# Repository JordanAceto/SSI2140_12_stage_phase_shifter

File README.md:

# SSI2140 Phase Shifter

---

## [SCHEMATIC](https://github.com/JordanAceto/SSI2140_12_stage_phase_shifter/blob/main/main_pcb/docs/SSI2140_phase_shifter-schematic.pdf)

---

### Features
- Eurorack 12 stage phase shifter
- Selectable number of stages (2, 4, 6, and 12)
- Positive and negative feedback
- Positive and negative wet/dry mix
- 1 attenuated CV input with approximately 1V/OCT response

---

## Status of the project:

Task | Status |
---------|--------------|
Schematic capture | &#9745;
PCB layout | &#9745;
Test build | &#9745;
Safe to order boards| &#9745;

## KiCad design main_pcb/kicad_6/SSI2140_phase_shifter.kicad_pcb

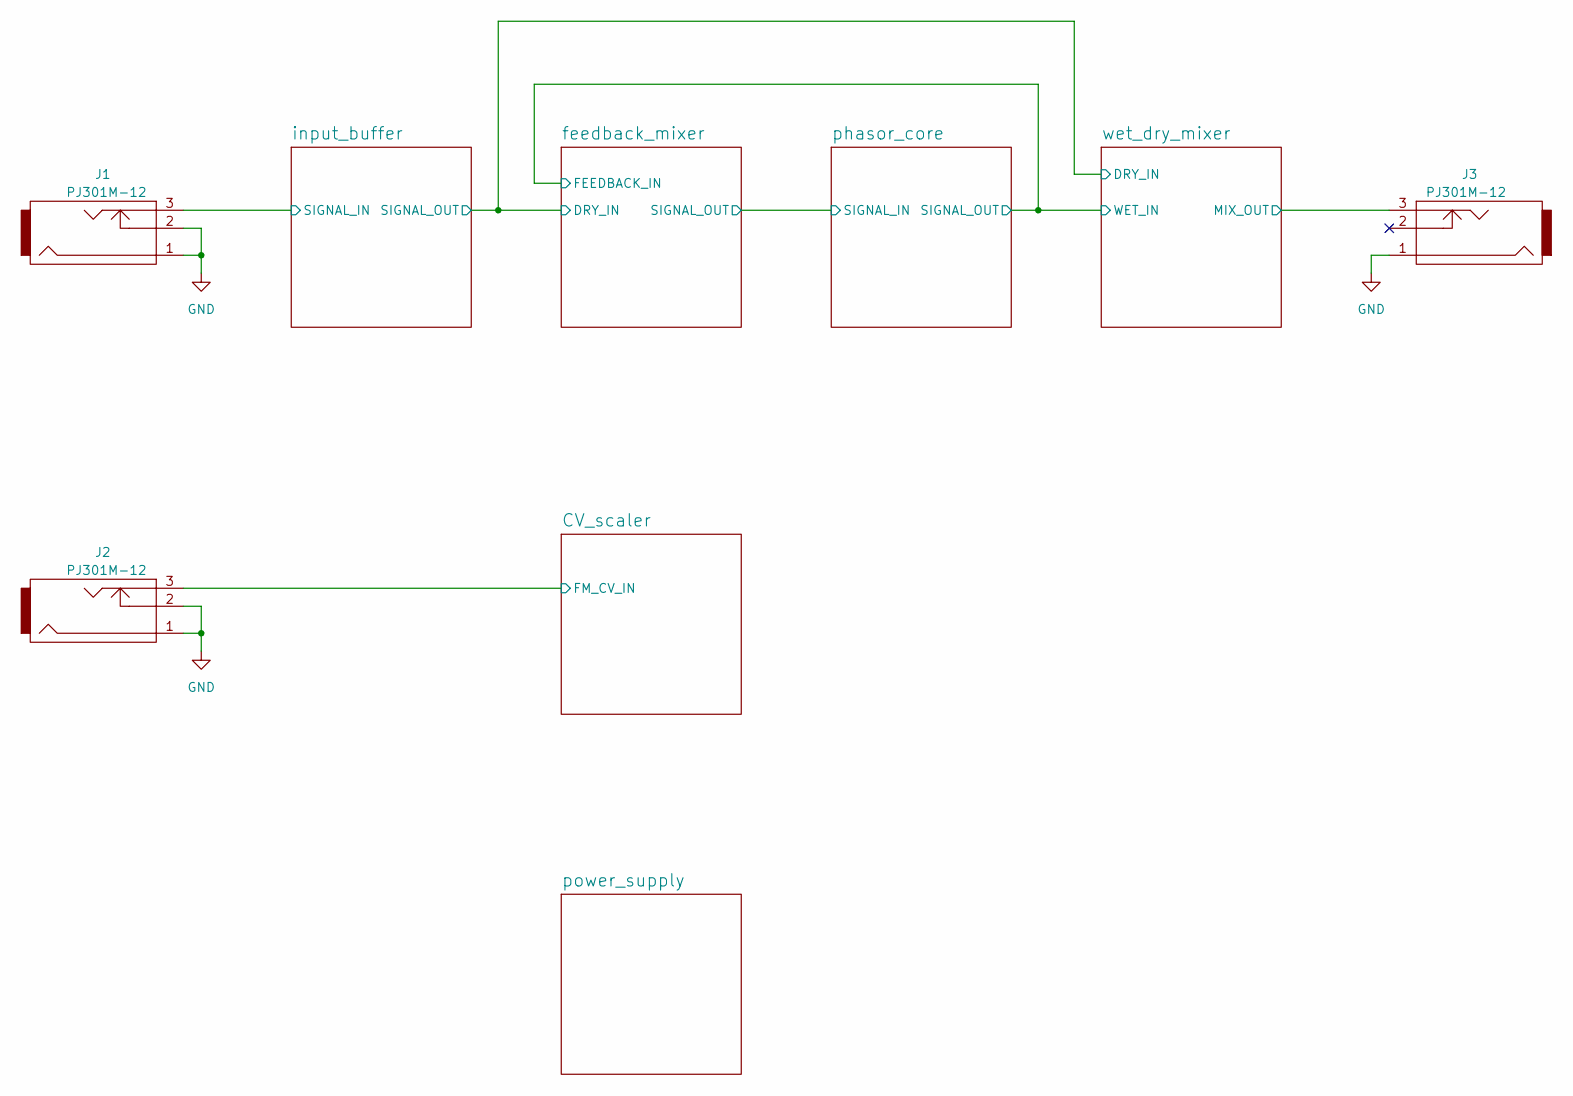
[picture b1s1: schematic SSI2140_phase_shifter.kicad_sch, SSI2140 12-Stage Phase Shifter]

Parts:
J1, J2, J3: PJ301M-12

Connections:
/CV_scaler/FM_CV_IN: J2.3; also elsewhere on the board
/input_buffer/SIGNAL_IN: J1.3; also elsewhere on the board
/wet_dry_mixer/MIX_OUT: J3.3; also elsewhere on the board
GND: J1.1, J1.2, J2.1, J2.2, J3.1; also elsewhere on the board

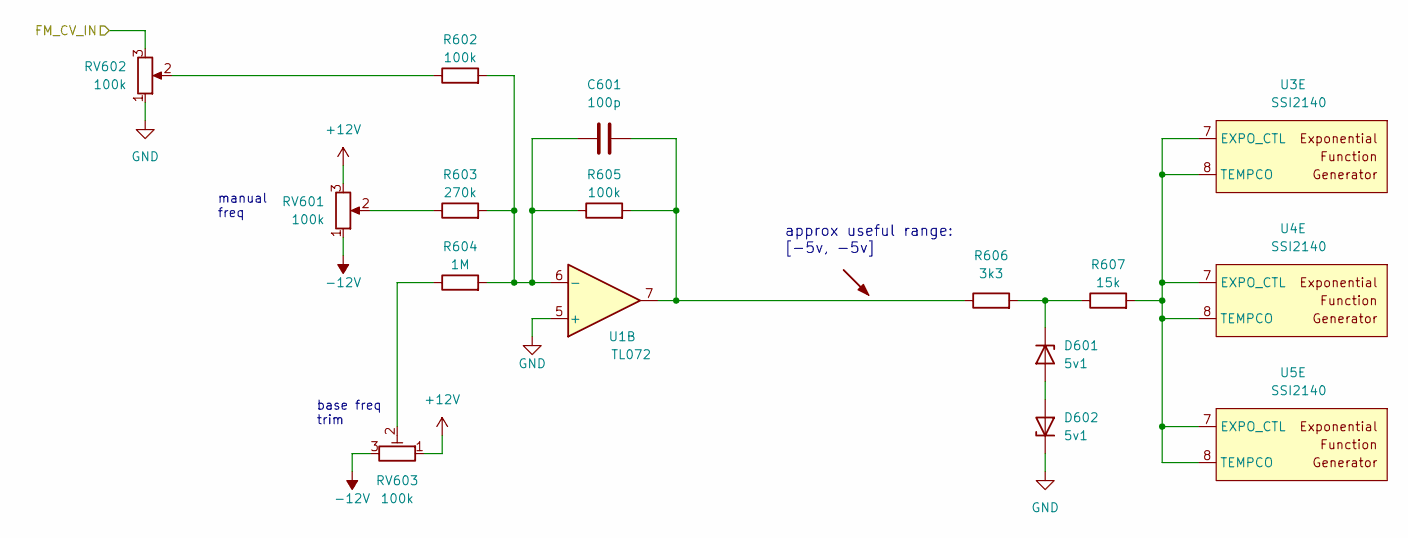
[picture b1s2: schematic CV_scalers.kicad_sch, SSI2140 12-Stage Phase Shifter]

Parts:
C601: 100p; C_0603_1608Metric
D601, D602: 5v1; D_SOD-123
R602, R605: 100k; R_0603_1608Metric
R603: 270k; R_0603_1608Metric
R604: 1M; R_0603_1608Metric
R606: 3k3; R_0603_1608Metric
R607: 15k; R_0603_1608Metric
RV601, RV602: 100k; Potentiometer_Alpha_RD901F-40-00D_Single_Vertical
RV603: 100k; Potentiometer_Bourns_3296W_Vertical
U1: TL072; SOIC-8_3.9x4.9mm_P1.27mm
U3, U4, U5: SSI2140; TSSOP-20_4.4x6.5mm_P0.65mm

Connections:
+12V: RV601.3, RV603.1; also elsewhere on the board
-12V: RV601.1, RV603.3; also elsewhere on the board
/CV_scaler/FM_CV_IN: RV602.3; also elsewhere on the board
GND: D602.1 (K), RV602.1, U1.5 (+); also elsewhere on the board
unnamed: C601.1, R602.2, R603.2, R604.2, R605.1, U1.6 (-)
unnamed: C601.2, R605.2, R606.1, U1.7
unnamed: D601.1 (K), R606.2, R607.1
unnamed: D601.2 (A), D602.2 (A)
unnamed: R602.1, RV602.2
unnamed: R603.1, RV601.2
unnamed: R604.1, RV603.2
unnamed: R607.2, U3.7 (EXPO_CTL), U3.8 (TEMPCO), U4.7 (EXPO_CTL), U4.8 (TEMPCO), U5.7 (EXPO_CTL), U5.8 (TEMPCO)

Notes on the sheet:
base freq trim
manual freq
approx useful range: [-5v, -5v]

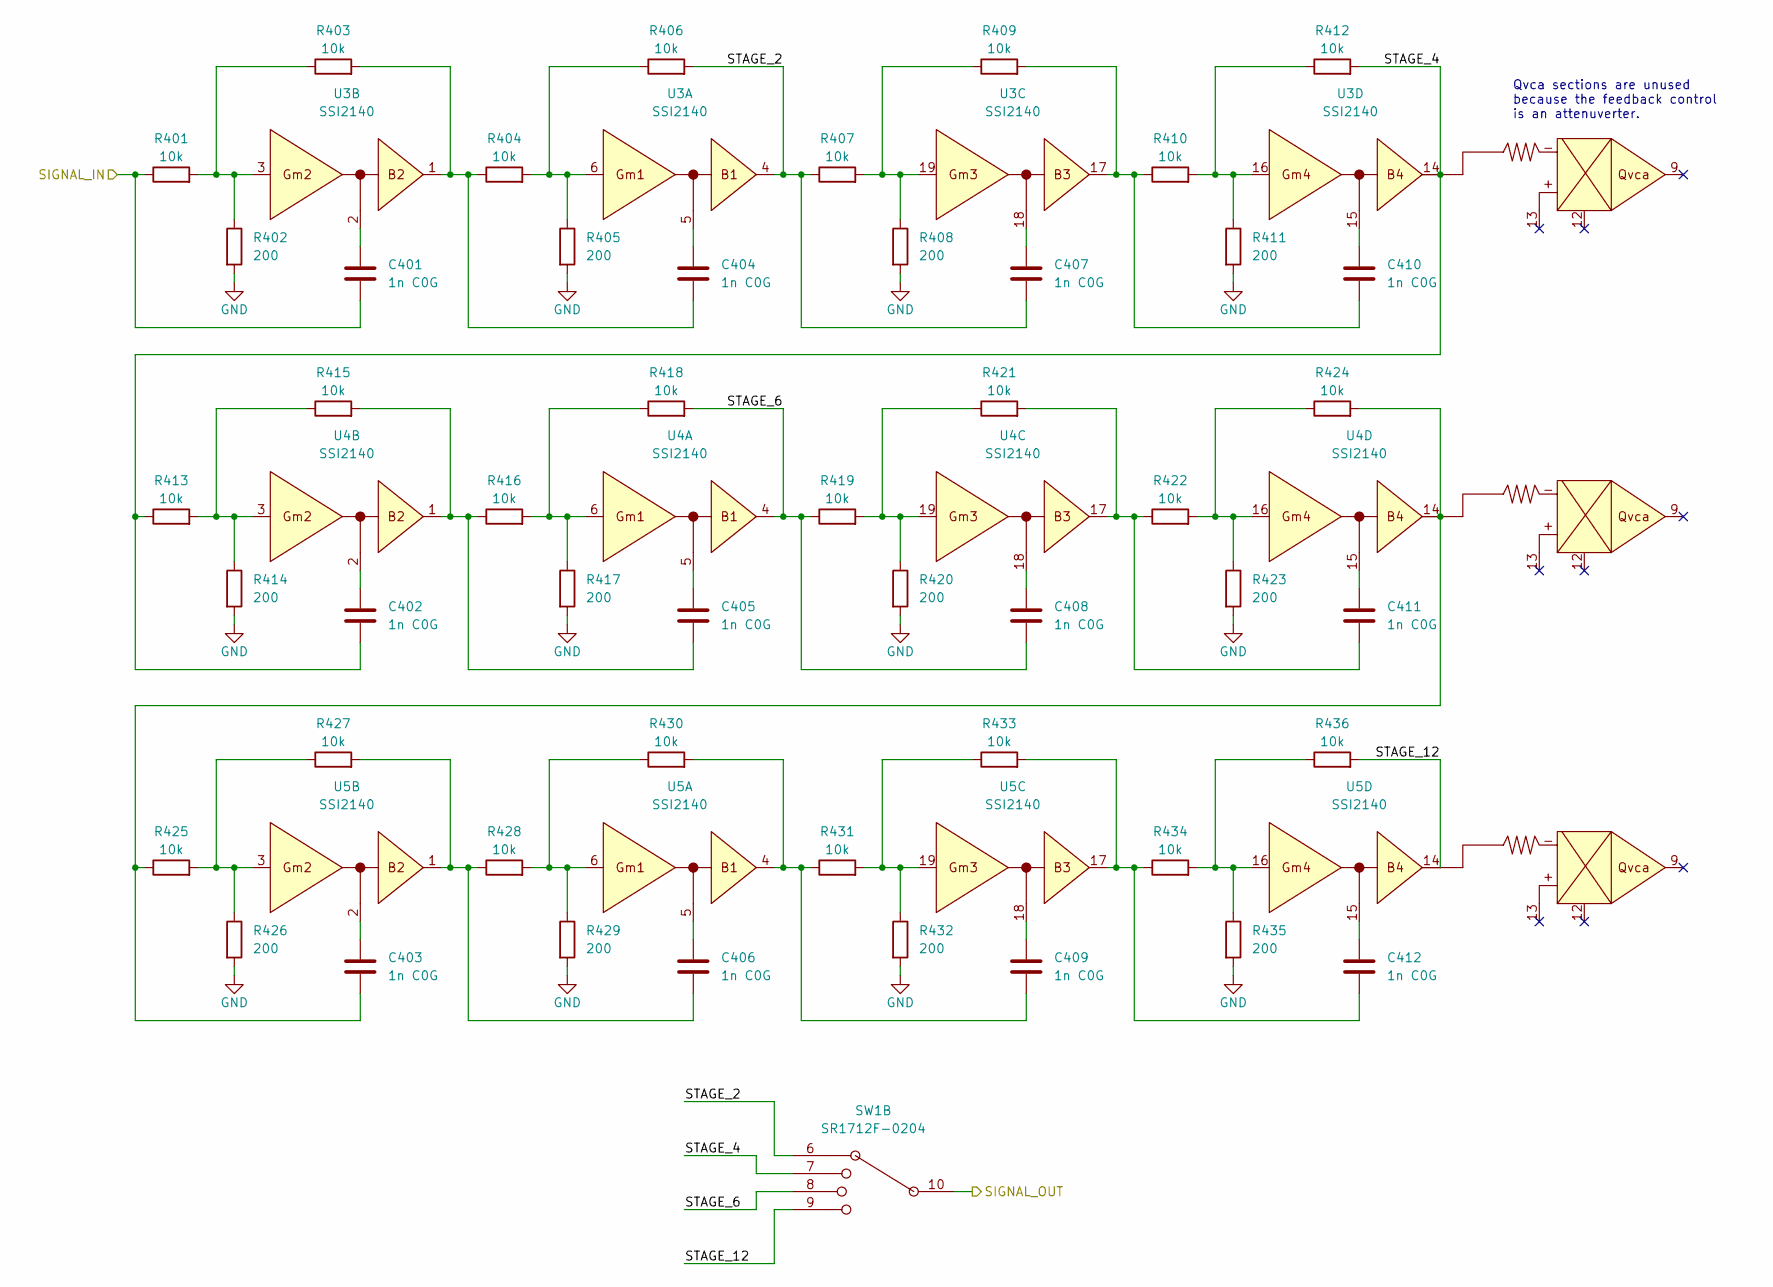
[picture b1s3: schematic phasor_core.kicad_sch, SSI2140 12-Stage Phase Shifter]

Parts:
C401, C402, C403, C404, C405, C406, C407, C408, C409, C410, C411, C412: 1n C0G; C_0805_2012Metric
R401, R403, R404, R406, R407, R409, R410, R412, R413, R415, R416, R418, R419, R421, R422, R424, R425, R427, R428, R430, R431, R433, R434, R436: 10k; R_0603_1608Metric
R402, R405, R408, R411, R414, R417, R420, R423, R426, R429, R432, R435: 200; R_0603_1608Metric
SW1: SR1712F-0204; SR1712F_rotary_switch
U3, U4, U5: SSI2140; TSSOP-20_4.4x6.5mm_P0.65mm

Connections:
/feedback_mixer/FEEDBACK_IN: SW1.10; also elsewhere on the board
/feedback_mixer/SIGNAL_OUT: C401.2, R401.1; also elsewhere on the board
/phasor_core/STAGE_2: C407.2, R406.2, R407.1, SW1.6, U3.4
/phasor_core/STAGE_4: C402.2, R412.2, R413.1, SW1.7, U3.14
/phasor_core/STAGE_6: C408.2, R418.2, R419.1, SW1.8, U4.4
/phasor_core/STAGE_12: R436.2, SW1.9, U5.14
GND: R402.2, R405.2, R408.2, R411.2, R414.2, R417.2, R420.2, R423.2, R426.2, R429.2, R432.2, R435.2; also elsewhere on the board
unnamed: C401.1, U3.2
unnamed: C402.1, U4.2
unnamed: C403.1, U5.2
unnamed: C403.2, R424.2, R425.1, U4.14
unnamed: C404.1, U3.5
unnamed: C404.2, R403.2, R404.1, U3.1
unnamed: C405.1, U4.5
unnamed: C405.2, R415.2, R416.1, U4.1
unnamed: C406.1, U5.5
unnamed: C406.2, R427.2, R428.1, U5.1
unnamed: C407.1, U3.18
unnamed: C408.1, U4.18
unnamed: C409.1, U5.18
unnamed: C409.2, R430.2, R431.1, U5.4
unnamed: C410.1, U3.15
unnamed: C410.2, R409.2, R410.1, U3.17
unnamed: C411.1, U4.15
unnamed: C411.2, R421.2, R422.1, U4.17
unnamed: C412.1, U5.15
unnamed: C412.2, R433.2, R434.1, U5.17
unnamed: R401.2, R402.1, R403.1, U3.3
unnamed: R404.2, R405.1, R406.1, U3.6
unnamed: R407.2, R408.1, R409.1, U3.19
unnamed: R410.2, R411.1, R412.1, U3.16
unnamed: R413.2, R414.1, R415.1, U4.3
unnamed: R416.2, R417.1, R418.1, U4.6
unnamed: R419.2, R420.1, R421.1, U4.19
unnamed: R422.2, R423.1, R424.1, U4.16
unnamed: R425.2, R426.1, R427.1, U5.3
unnamed: R428.2, R429.1, R430.1, U5.6
unnamed: R431.2, R432.1, R433.1, U5.19
unnamed: R434.2, R435.1, R436.1, U5.16

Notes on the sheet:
Qvca sections are unused because the feedback control is an attenuverter.

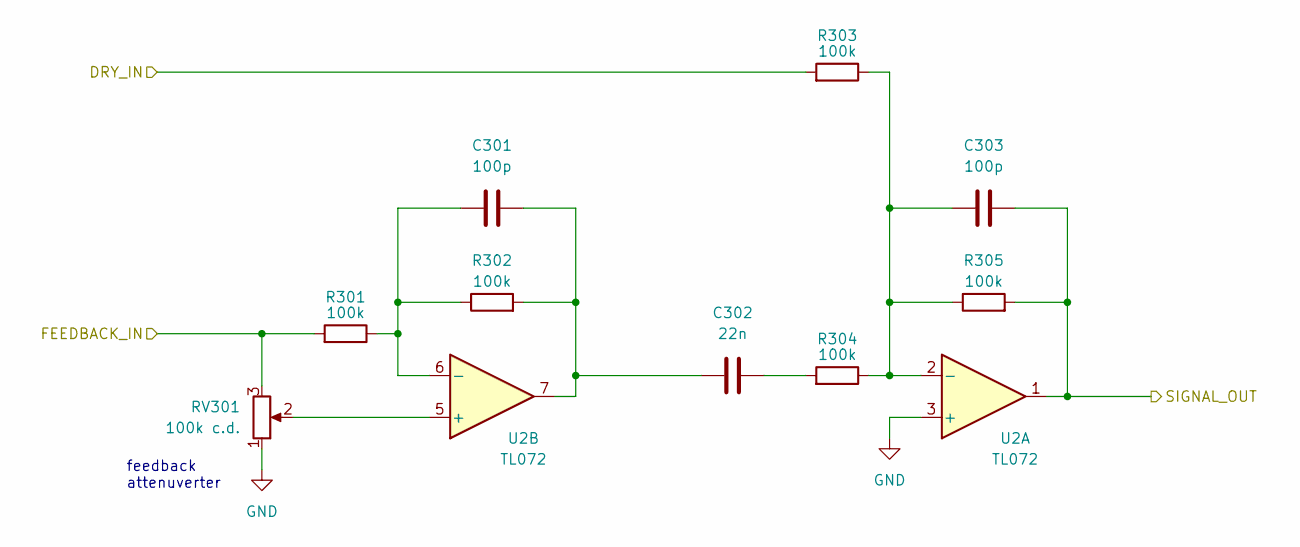
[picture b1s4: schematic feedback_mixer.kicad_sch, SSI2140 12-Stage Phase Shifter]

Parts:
C301, C303: 100p; C_0603_1608Metric
C302: 22n; C_Rect_L7.0mm_W2.5mm_P5.00mm
R301, R302, R303, R304, R305: 100k; R_0603_1608Metric
RV301: 100k c.d.; Potentiometer_Alpha_RD901F-40-00D_Single_Vertical
U2: TL072; SOIC-8_3.9x4.9mm_P1.27mm

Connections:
/feedback_mixer/DRY_IN: R303.2; also elsewhere on the board
/feedback_mixer/FEEDBACK_IN: R301.2, RV301.3; also elsewhere on the board
/feedback_mixer/SIGNAL_OUT: C303.1, R305.2, U2.1; also elsewhere on the board
GND: RV301.1, U2.3 (+); also elsewhere on the board
unnamed: C301.1, C302.1, R302.2, U2.7
unnamed: C301.2, R301.1, R302.1, U2.6 (-)
unnamed: C302.2, R304.2
unnamed: C303.2, R303.1, R304.1, R305.1, U2.2 (-)
unnamed: RV301.2, U2.5 (+)

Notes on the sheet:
feedback attenuverter

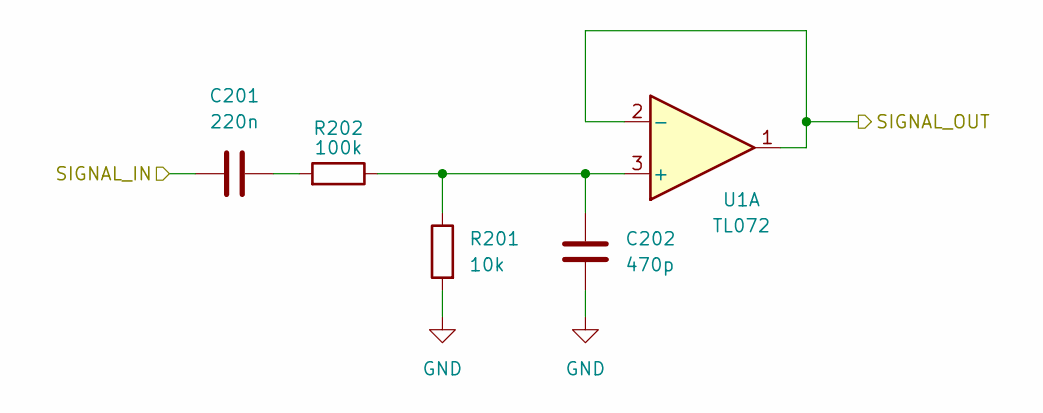
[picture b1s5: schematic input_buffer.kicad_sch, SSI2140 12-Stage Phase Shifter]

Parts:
C201: 220n; C_Rect_L7.0mm_W2.5mm_P5.00mm
C202: 470p; C_0603_1608Metric
R201: 10k; R_0603_1608Metric
R202: 100k; R_0603_1608Metric
U1: TL072; SOIC-8_3.9x4.9mm_P1.27mm

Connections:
/feedback_mixer/DRY_IN: U1.1, U1.2 (-); also elsewhere on the board
/input_buffer/SIGNAL_IN: C201.2; also elsewhere on the board
GND: C202.1, R201.2; also elsewhere on the board
unnamed: C201.1, R202.2
unnamed: C202.2, R201.1, R202.1, U1.3 (+)

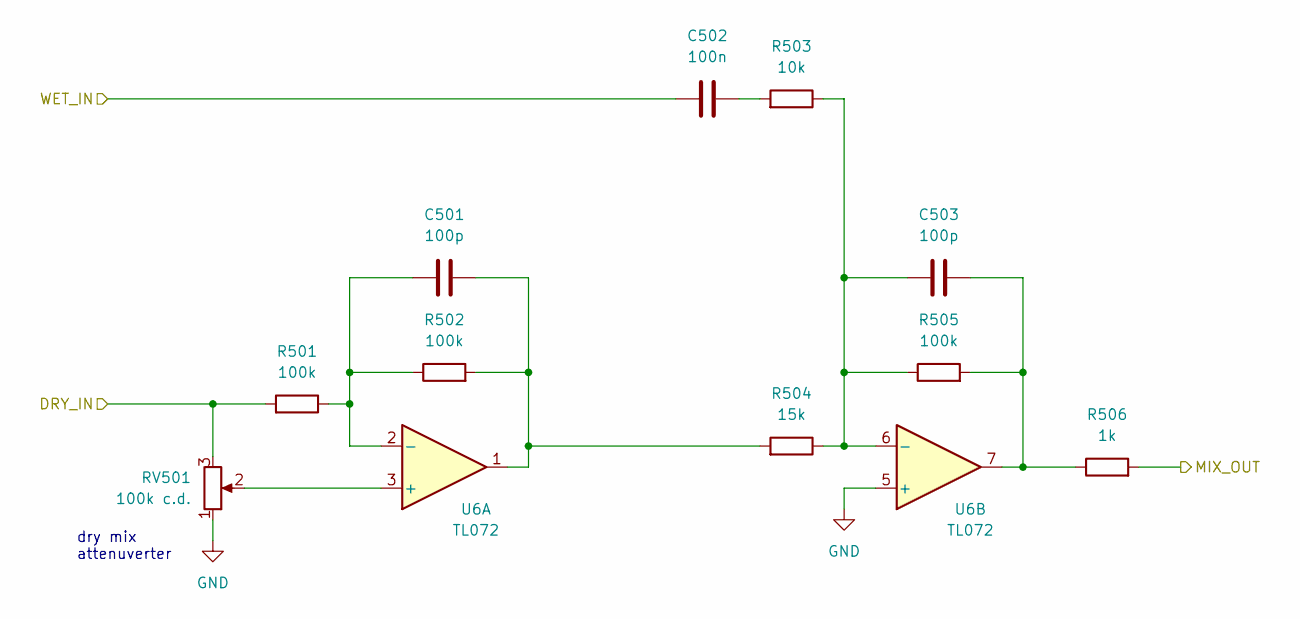
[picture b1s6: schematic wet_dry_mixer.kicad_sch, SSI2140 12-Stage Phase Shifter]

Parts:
C501, C503: 100p; C_0603_1608Metric
C502: 100n; C_Rect_L7.0mm_W2.5mm_P5.00mm
R501, R502, R505: 100k; R_0603_1608Metric
R503: 10k; R_0603_1608Metric
R504: 15k; R_0603_1608Metric
R506: 1k; R_0603_1608Metric
RV501: 100k c.d.; Potentiometer_Alpha_RD901F-40-00D_Single_Vertical
U6: TL072; SOIC-8_3.9x4.9mm_P1.27mm

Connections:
/feedback_mixer/DRY_IN: R501.2, RV501.3; also elsewhere on the board
/feedback_mixer/FEEDBACK_IN: C502.1; also elsewhere on the board
/wet_dry_mixer/MIX_OUT: R506.2; also elsewhere on the board
GND: RV501.1, U6.5 (+); also elsewhere on the board
unnamed: C501.1, R502.2, R504.2, U6.1
unnamed: C501.2, R501.1, R502.1, U6.2 (-)
unnamed: C502.2, R503.2
unnamed: C503.1, R505.2, R506.1, U6.7
unnamed: C503.2, R503.1, R504.1, R505.1, U6.6 (-)
unnamed: RV501.2, U6.3 (+)

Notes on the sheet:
dry mix attenuverter

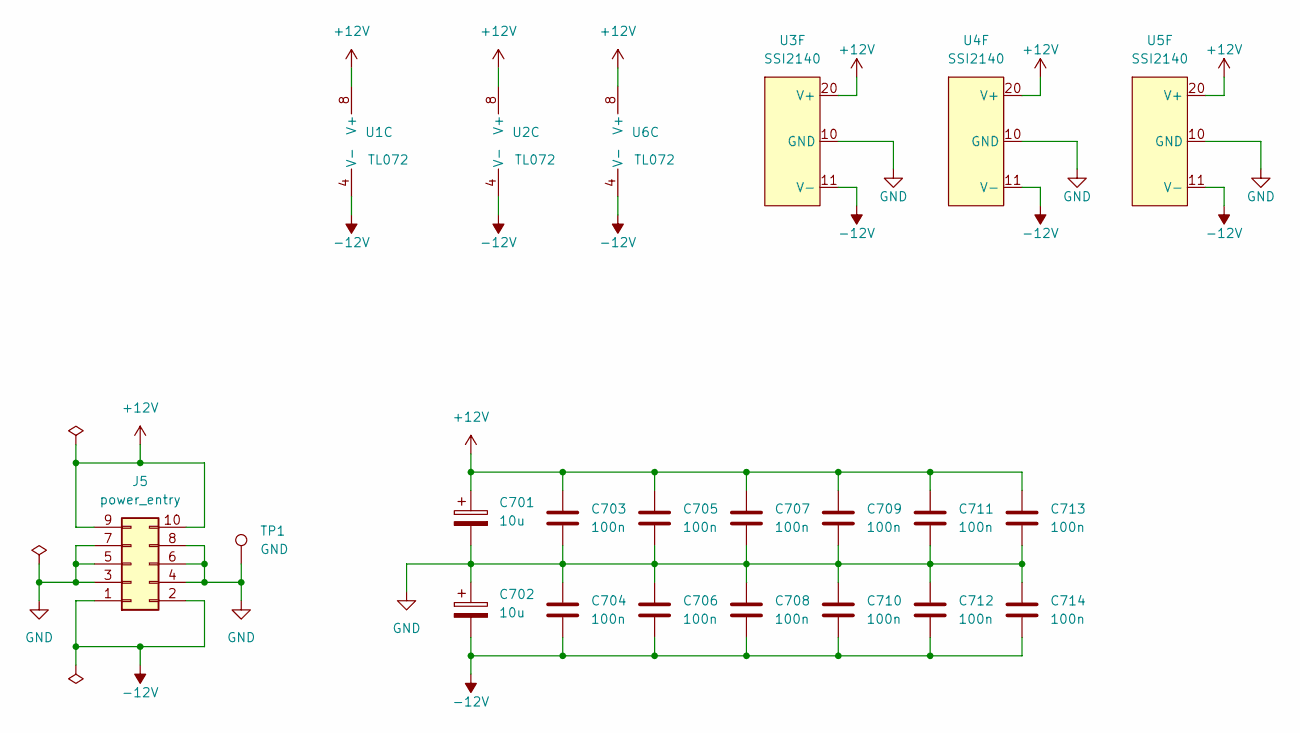
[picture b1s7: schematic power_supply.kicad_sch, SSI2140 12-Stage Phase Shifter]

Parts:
C701, C702: 10u; CP_Radial_D6.3mm_P2.50mm
C703, C704, C705, C706, C707, C708, C709, C710, C711, C712, C713, C714: 100n; C_0603_1608Metric
J5: power_entry; PinHeader_2x05_P2.54mm_Vertical
TP1: GND; TestPoint_Bridge_Pitch7.62mm_Drill1.3mm
U1, U2, U6: TL072; SOIC-8_3.9x4.9mm_P1.27mm
U3, U4, U5: SSI2140; TSSOP-20_4.4x6.5mm_P0.65mm

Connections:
+12V: C701.1, C703.1, C705.1, C707.1, C709.1, C711.1, C713.1, J5.9, J5.10, U1.8 (V+), U2.8 (V+), U3.20 (V+), U4.20 (V+), U5.20 (V+), U6.8 (V+); also elsewhere on the board
-12V: C702.2, C704.2, C706.2, C708.2, C710.2, C712.2, C714.2, J5.1, J5.2, U1.4 (V-), U2.4 (V-), U3.11 (V-), U4.11 (V-), U5.11 (V-), U6.4 (V-); also elsewhere on the board
GND: C701.2, C702.1, C703.2, C704.1, C705.2, C706.1, C707.2, C708.1, C709.2, C710.1, C711.2, C712.1, C713.2, C714.1, J5.3, J5.4, J5.5, J5.6, J5.7, J5.8, TP1.1, U3.10 (GND), U4.10 (GND), U5.10 (GND); also elsewhere on the board

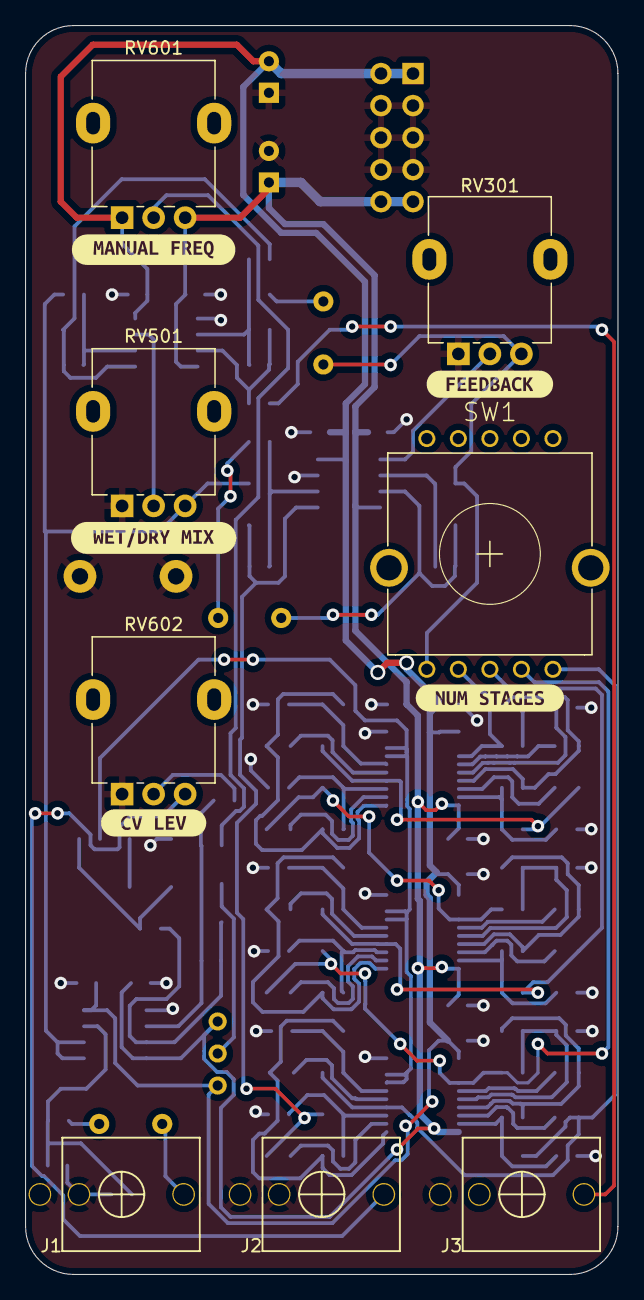
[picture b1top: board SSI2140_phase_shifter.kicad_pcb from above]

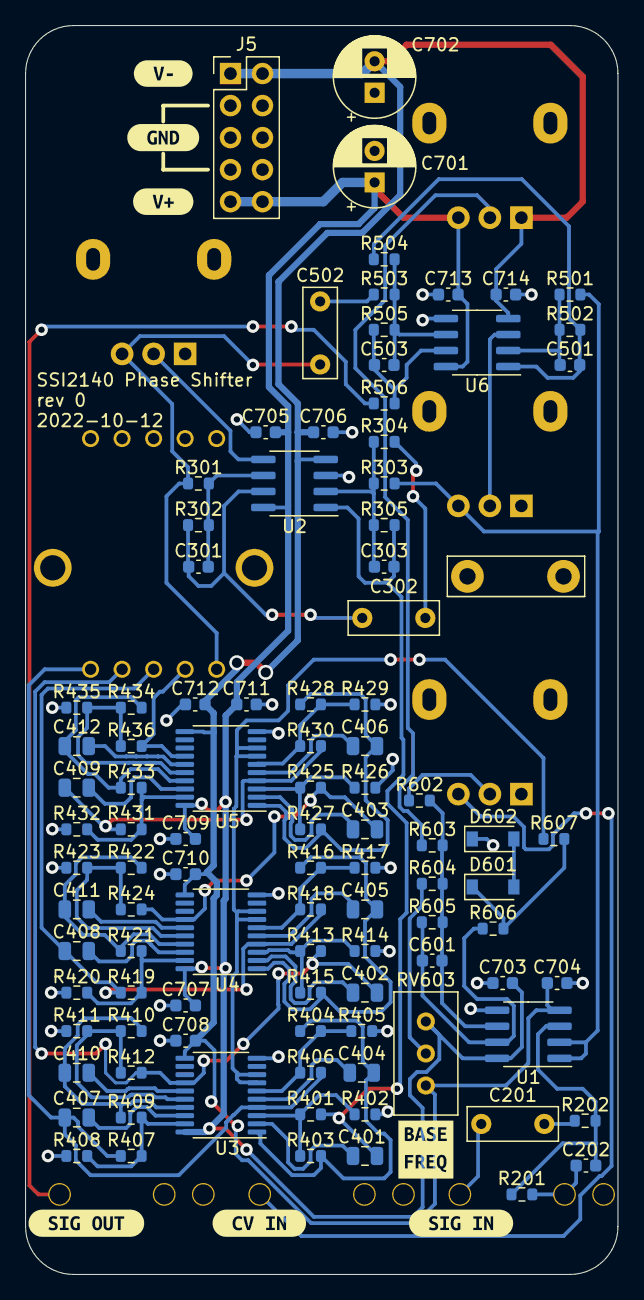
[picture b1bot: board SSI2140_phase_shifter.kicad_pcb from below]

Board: 2 copper layers, 47.0 x 99.1 mm, 121 parts (108 on the bottom side), 66 nets.

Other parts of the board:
kibuzzard-6346B9B0: G***; kibuzzard-6346B9B0
kibuzzard-6346B9BA: G***; kibuzzard-6346B9BA
kibuzzard-6346B9C8: G***; kibuzzard-6346B9C8
kibuzzard-6346BA4D: G***; kibuzzard-6346BA4D
kibuzzard-6346BA5C: G***; kibuzzard-6346BA5C
kibuzzard-6346BA18: G***; kibuzzard-6346BA18
kibuzzard-6346BA34: G***; kibuzzard-6346BA34
kibuzzard-6346BB8C: G***; kibuzzard-6346BB8C
kibuzzard-6346BB9C: G***; kibuzzard-6346BB9C
kibuzzard-6346BBAC: G***; kibuzzard-6346BBAC
kibuzzard-6346BBB6: G***; kibuzzard-6346BBB6
kibuzzard-6346BBC8: G***; kibuzzard-6346BBC8

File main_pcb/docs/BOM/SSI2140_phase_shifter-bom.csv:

Row,Description,Part,References,Value,Footprint,Quantity Per PCB,Status,Datasheet
1,Unpolarized capacitor,C,C301 C303 C501 C503 C601,100p,C_0603_1608Metric,5, ,~
2,Unpolarized capacitor,C,C202,470p,C_0603_1608Metric,1, ,~
3,Unpolarized capacitor,C,C401 C402 C403 C404 C405 C406 C407 C408 C409 C410 C411 C412,1n C0G,C_0805_2012Metric,12, ,~
4,Unpolarized capacitor,C,C302,22n,C_Rect_L7.0mm_W2.5mm_P5.00mm,1, ,~
5,Unpolarized capacitor,C,C502,100n,C_Rect_L7.0mm_W2.5mm_P5.00mm,1, ,~
6,Unpolarized capacitor,C,C703 C704 C705 C706 C707 C708 C709 C710 C711 C712 C713 C714,100n,C_0603_1608Metric,12, ,~
7,Unpolarized capacitor,C,C201,220n,C_Rect_L7.0mm_W2.5mm_P5.00mm,1, ,~
8,Polarized capacitor,C_Polarized,C701 C702,10u,CP_Radial_D6.3mm_P2.50mm,2, ,~
9,Zener diode,D_Zener,D601 D602,5v1,D_SOD-123,2, ,~
10,,PJ301M-12,J1 J2 J3,PJ301M-12,PJ301M-12,3, ,
11,"Generic connector, double row, 02x05, odd/even pin numbering scheme (row 1 odd numbers, row 2 even numbers), script generated (kicad-library-utils/schlib/autogen/connector/)",Conn_02x05_Odd_Even,J5,power_entry,PinHeader_2x05_P2.54mm_Vertical,1, ,~
12,Resistor,R,R402 R405 R408 R411 R414 R417 R420 R423 R426 R429 R432 R435,200,R_0603_1608Metric,12, ,~
13,Resistor,R,R506,1k,R_0603_1608Metric,1, ,~
14,Resistor,R,R606,3k3,R_0603_1608Metric,1, ,~
15,Resistor,R,R201 R401 R403 R404 R406 R407 R409 R410 R412 R413 R415 R416 R418 R419 R421 R422 R424 R425 R427 R428 R430 R431 R433 R434 R436 R503,10k,R_0603_1608Metric,26, ,~
16,Resistor,R,R504 R607,15k,R_0603_1608Metric,2, ,~
17,Resistor,R,R202 R301 R302 R303 R304 R305 R501 R502 R505 R602 R605,100k,R_0603_1608Metric,11, ,~
18,Resistor,R,R603,270k,R_0603_1608Metric,1, ,~
19,Resistor,R,R604,1M,R_0603_1608Metric,1, ,~
20,Potentiometer,R_Potentiometer,RV301 RV501 RV601 RV602,100k c.d.,Potentiometer_Alpha_RD901F-40-00D_Single_Vertical,4, ,~
21,Trim-potentiometer,R_Potentiometer_Trim,RV603,100k,Potentiometer_Bourns_3296W_Vertical,1, ,~
22,3 rotary switches with 4 positions,SR1712F-0204,SW1,SR1712F-0204,SR1712F_rotary_switch,1, ,
23,,SSI2140,U3 U4 U5,SSI2140,TSSOP-20_4.4x6.5mm_P0.65mm,3, ,
24,"Dual Low-Noise JFET-Input Operational Amplifiers, DIP-8/SOIC-8",TL072,U1 U2 U6,TL072,SOIC-8_3.9x4.9mm_P1.27mm,3, ,http://www.ti.com/lit/ds/symlink/tl071.pdf





Project info:
Schematic:,SSI2140_phase_shifter
Variant:,default
Revision:,0
Date:,2022-10-11
KiCad Version:,6.0.5+dfsg-1~bpo11+1
Statistics:
Component Groups:,24
Component Count:,108 (87 SMD/ 15 THT)
Fitted Components:,108 (87 SMD/ 15 THT)
Number of PCBs:,1
Total Components:,108

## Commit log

2022-12-29 Add license
2022-12-29 Add schematic link

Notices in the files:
main_pcb/kicad_6/CV_scalers.kicad_sch:
creativecommons.org/licences/by/4.0
Licence: CC by 4.0
main_pcb/kicad_6/SSI2140_phase_shifter.kicad_pcb:
creativecommons.org/licenses/by/4.0
License: CC by 4.0
